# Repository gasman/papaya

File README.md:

# papAYa
an AY-3-8912 sound chip expansion board for the Raspberry Pi

## Why?
[I do ZX Spectrum chiptune performances](http://gasman.zxdemo.org/), but taking an entire ZX Spectrum setup to a venue is a faff, especially at gigs where the organisers are more used to people rocking up with a Gameboy, plugging in a jack and being ready to play. Some of the tracks I play require two sound chips, and taking two Spectrums would be even more of a faff.

Sure, you can emulate it, and honestly the AY is well-understood and deterministic enough that it would make no difference to the sound. But if you take that attitude, then what's the point of live music anyhow? I figure you don't need a 1980s-vintage Spectrum to be authentic, but you do at least need the actual sound chip.

Basically, I want to be as cool as the Gameboy folks. I want to get up on stage and make magic happen from a handheld device like I'm piloting a goddamn spaceship. And the best way to do that is to hook up an AY chip (or two) to a Raspberry Pi.

## What's here

* `papaya/` - KiCad files for the single-AY board
* `papaya2/` - KiCad files for the double-AY board
* `player/` - Command-line players for .psg files (as exported by [AY Emulator](https://bulba.untergrund.net/emulator_e.htm) and [Fuse](http://fuse-emulator.sourceforge.net/)). Requires [pigpio](http://abyz.me.uk/rpi/pigpio/) to build.
  * `player/psg` - plays a single-AY track in .psg format. Run with `sudo ./psg somefile.psg`
  * `player/psg2` - plays a dual-AY track exported as two .psg files. Run with `sudo ./psg2 somefile1.psg somefile2.psg`
* `server/` - Server software; see below
* `client/` - Client software to communicate with the papaya server
* `psgfiles/` - some example .psg files

## Bill of materials

For the single-AY board:
* Papaya v1 PCB
* P1 - 2x20 pin GPIO header https://www.adafruit.com/product/2222
* J1 - dual RCA connector [PJRAN2X1U01AUX](https://www.mouser.co.uk/ProductDetail/Switchcraft/PJRAN2X1U01AUX?qs=mcPJWgAPNre69iQqys4MXw%3D%3D)
* U1 - AY-3-8912 sound chip (_not_ AY-3-8912A - see below)
* R1, R2 - 10k resistor
* R3, R4 - 15k resistor

For the dual-AY board:

* Papaya 2 PCB
* P1 - 2x20 pin GPIO header https://www.adafruit.com/product/2222
* J1 - dual RCA connector [PJRAN2X1U01AUX](https://www.mouser.co.uk/ProductDetail/Switchcraft/PJRAN2X1U01AUX?qs=mcPJWgAPNre69iQqys4MXw%3D%3D)
* U1, U2 - AY-3-8912 sound chip (_not_ AY-3-8912A - see below)
* R1, R2, R5, R6 - 10k resistor
* R3, R4, R7, R8 - 15k resistor

## Design considerations
The AY data bus (pins DA0-DA7) is connected directly to GPIO pins: 17, 27, 22, 10, 9, 11, 5, 6. The AY chip is a 5V device while the Raspberry Pi runs on 3.3V, but since the data direction is write-only and the AY accepts anything over 2.5V as logic high, no level conversion is needed.

For the first AY chip, BC1 is on GPIO pin 13 and BDIR is on pin 19. On the dual AY board, the second chip's BC1 is on pin 20 and BDIR is on pin 21. The clock signal is provided by the Raspberry Pi's hardware clock on GPIO pin 4. GPIO pin 26 is connected to RESET on both chips (NOTE: this is not implemented on the PCB yet).

Audio output is in ACB stereo format: channel A (of both chips) is mixed to the left, channel B to the right and C in the centre.

Some or all AY-3-8912A chips have a quirk where the RESET line must be toggled low then high in order to activate the noise generator - it does not function immediately on power-on. This is implemented in the software, but the PCB has not yet been updated to support this (the RESET line is held high instead) and so will currently only work with AY-3-8912 (not 8912A) chips.

Technically this board doesn't qualify as a HAT, as it doesn't include the identifying EPROM.

## Mounting
With socketed chips, the Raspberry Pi and papAYa combo fits neatly into a [SmartiPi Touch 2 case](https://thepihut.com/products/smartipi-touch-2) with a [15mm back cover](https://thepihut.com/products/smartipi-touch-2-back-cover), provided you use [11mm spacers](https://thepihut.com/products/raspberry-pi-hat-mounting-kit) rather than the slightly-taller ones that come with the touchscreen.

## Server
Rather than having each client program do its own low-level GPIO access (which typically requires running as root), the AY can be made available over a network service, running on TCP port 8912. See server/protocol.txt for details of the protocol.

To build, run `make` from the `server` directory - this requires [pigpio](http://abyz.me.uk/rpi/pigpio/). Copy the resulting `server` executable to `/usr/local/sbin/papaya`, and run it under supervisor using a configuration file such as (in `/etc/supervisor/conf.d/papaya.conf`):

    [program:papaya]
    command=/usr/local/sbin/papaya
    autostart=true
    autorestart=true

`client/psg.py` is a client program for playing .psg files, written in Python - run with:

    ./psg.py somefile.psg

Or, for multiple chips:

    ./psg.py somefile1.psg somefile2.psg

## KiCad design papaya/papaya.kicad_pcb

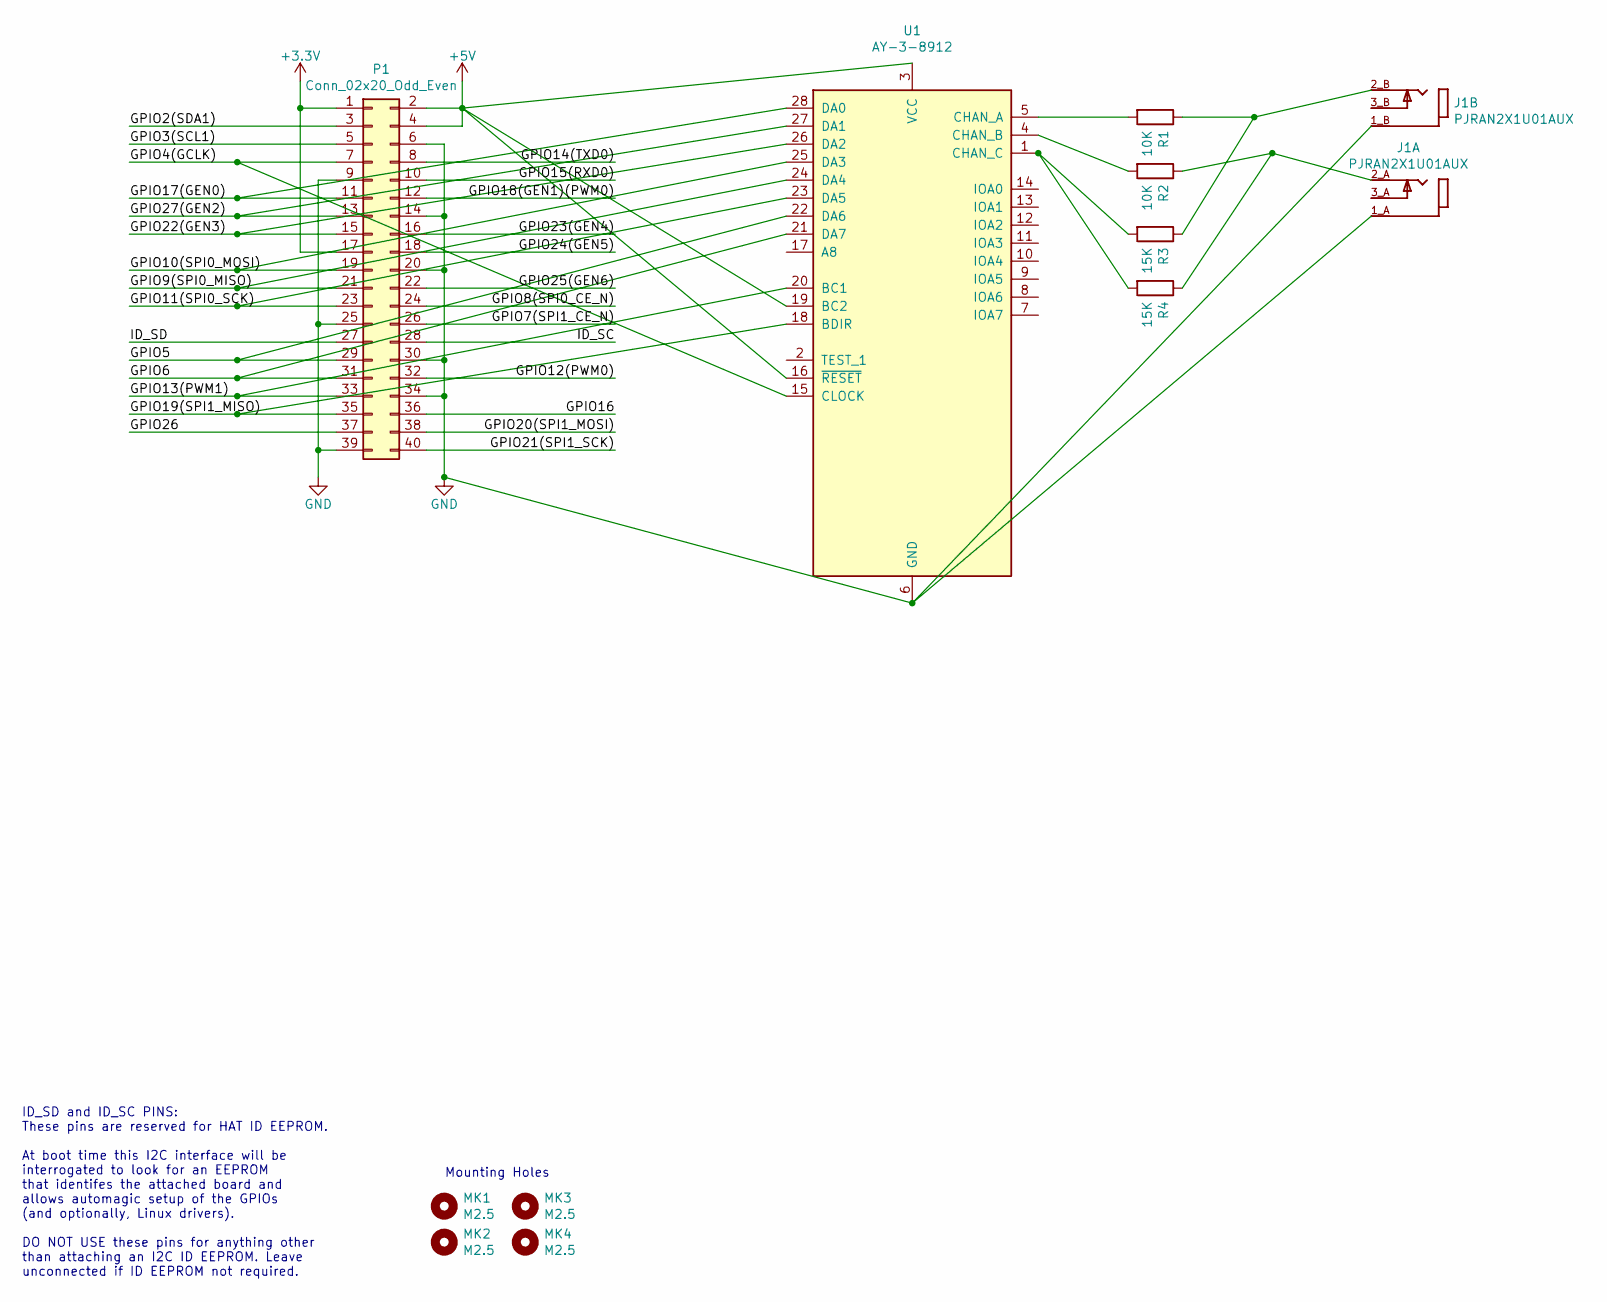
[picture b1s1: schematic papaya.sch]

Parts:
J1: PJRAN2X1U01AUX; SWITCHCRAFT_PJRAN2X1U01AUX
MK1, MK2, MK3, MK4: M2.5; MountingHole_2.7mm_M2.5
P1: Conn_02x20_Odd_Even; PinSocket_2x20_P2.54mm_Vertical
R1, R2: 10K; R_Axial_DIN0207_L6.3mm_D2.5mm_P10.16mm_Horizontal
R3, R4: 15K; R_Axial_DIN0207_L6.3mm_D2.5mm_P10.16mm_Horizontal
U1: AY-3-8912; DIP-28_W15.24mm_LongPads

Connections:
+3V3: P1.1, P1.17
+5V: P1.2, P1.4, U1.3 (VCC), U1.16 (~RESET~), U1.19 (BC2)
/GPIO2(SDA1): P1.3
/GPIO3(SCL1): P1.5
/GPIO5: P1.29, U1.22 (DA6)
/GPIO6: P1.31, U1.21 (DA7)
/GPIO8(SPI0_CE_N): P1.24
/GPIO9(SPI0_MISO): P1.21, U1.24 (DA4)
/GPIO10(SPI0_MOSI): P1.19, U1.25 (DA3)
/GPIO11(SPI0_SCK): P1.23, U1.23 (DA5)
/GPIO12(PWM0): P1.32
/GPIO13(PWM1): P1.33, U1.20 (BC1)
/GPIO14(TXD0): P1.8
/GPIO15(RXD0): P1.10
/GPIO16: P1.36
/GPIO17(GEN0): P1.11, U1.28 (DA0)
/GPIO18(GEN1)(PWM0): P1.12
/GPIO19(SPI1_MISO): P1.35, U1.18 (BDIR)
/GPIO20(SPI1_MOSI): P1.38
/GPIO21(SPI1_SCK): P1.40
/GPIO22(GEN3): P1.15, U1.26 (DA2)
/GPIO23(GEN4): P1.16
/GPIO24(GEN5): P1.18
/GPIO25(GEN6): P1.22
/GPIO26: P1.37
/GPIO27(GEN2): P1.13, U1.27 (DA1)
/ID_SC: P1.28
/ID_SD: P1.27
GND: J1.1_A (SLEEVE-A), J1.1_B (SLEEVE-B), P1.6, P1.9, P1.14, P1.20, P1.25, P1.30, P1.34, P1.39, U1.6 (GND)
unnamed: J1.2_A (TIP-A), R2.1, R4.1
unnamed: J1.2_B (TIP-B), R1.1, R3.1
unnamed: R1.2, U1.5 (CHAN_A)
unnamed: R2.2, U1.4 (CHAN_B)
unnamed: R3.2, R4.2, U1.1 (CHAN_C)

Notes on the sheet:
ID_SD and ID_SC PINS: These pins are reserved for HAT ID EEPROM. At boot time this I2C interface will be interrogated to look for an EEPROM that identifes the attached board and allows automagic setup of the GPIOs (and optionally, Linux drivers). DO NOT USE these pins for anything other than attach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
Mounting Holes

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
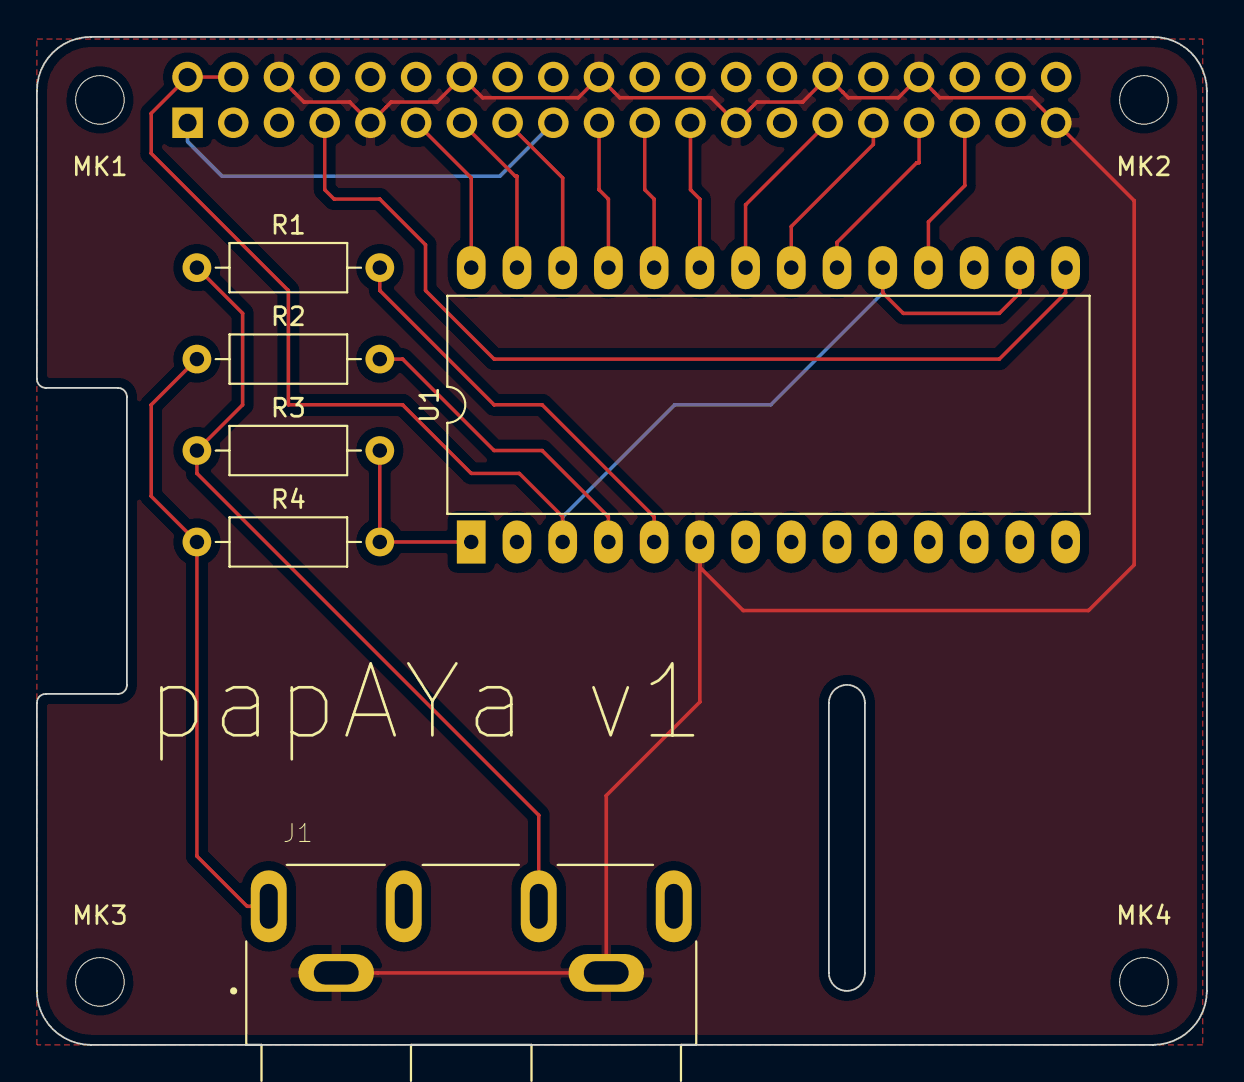
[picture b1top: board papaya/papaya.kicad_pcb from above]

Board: 2 copper layers, 65.0 x 56.0 mm, 11 parts (1 on the bottom side), 19 nets.

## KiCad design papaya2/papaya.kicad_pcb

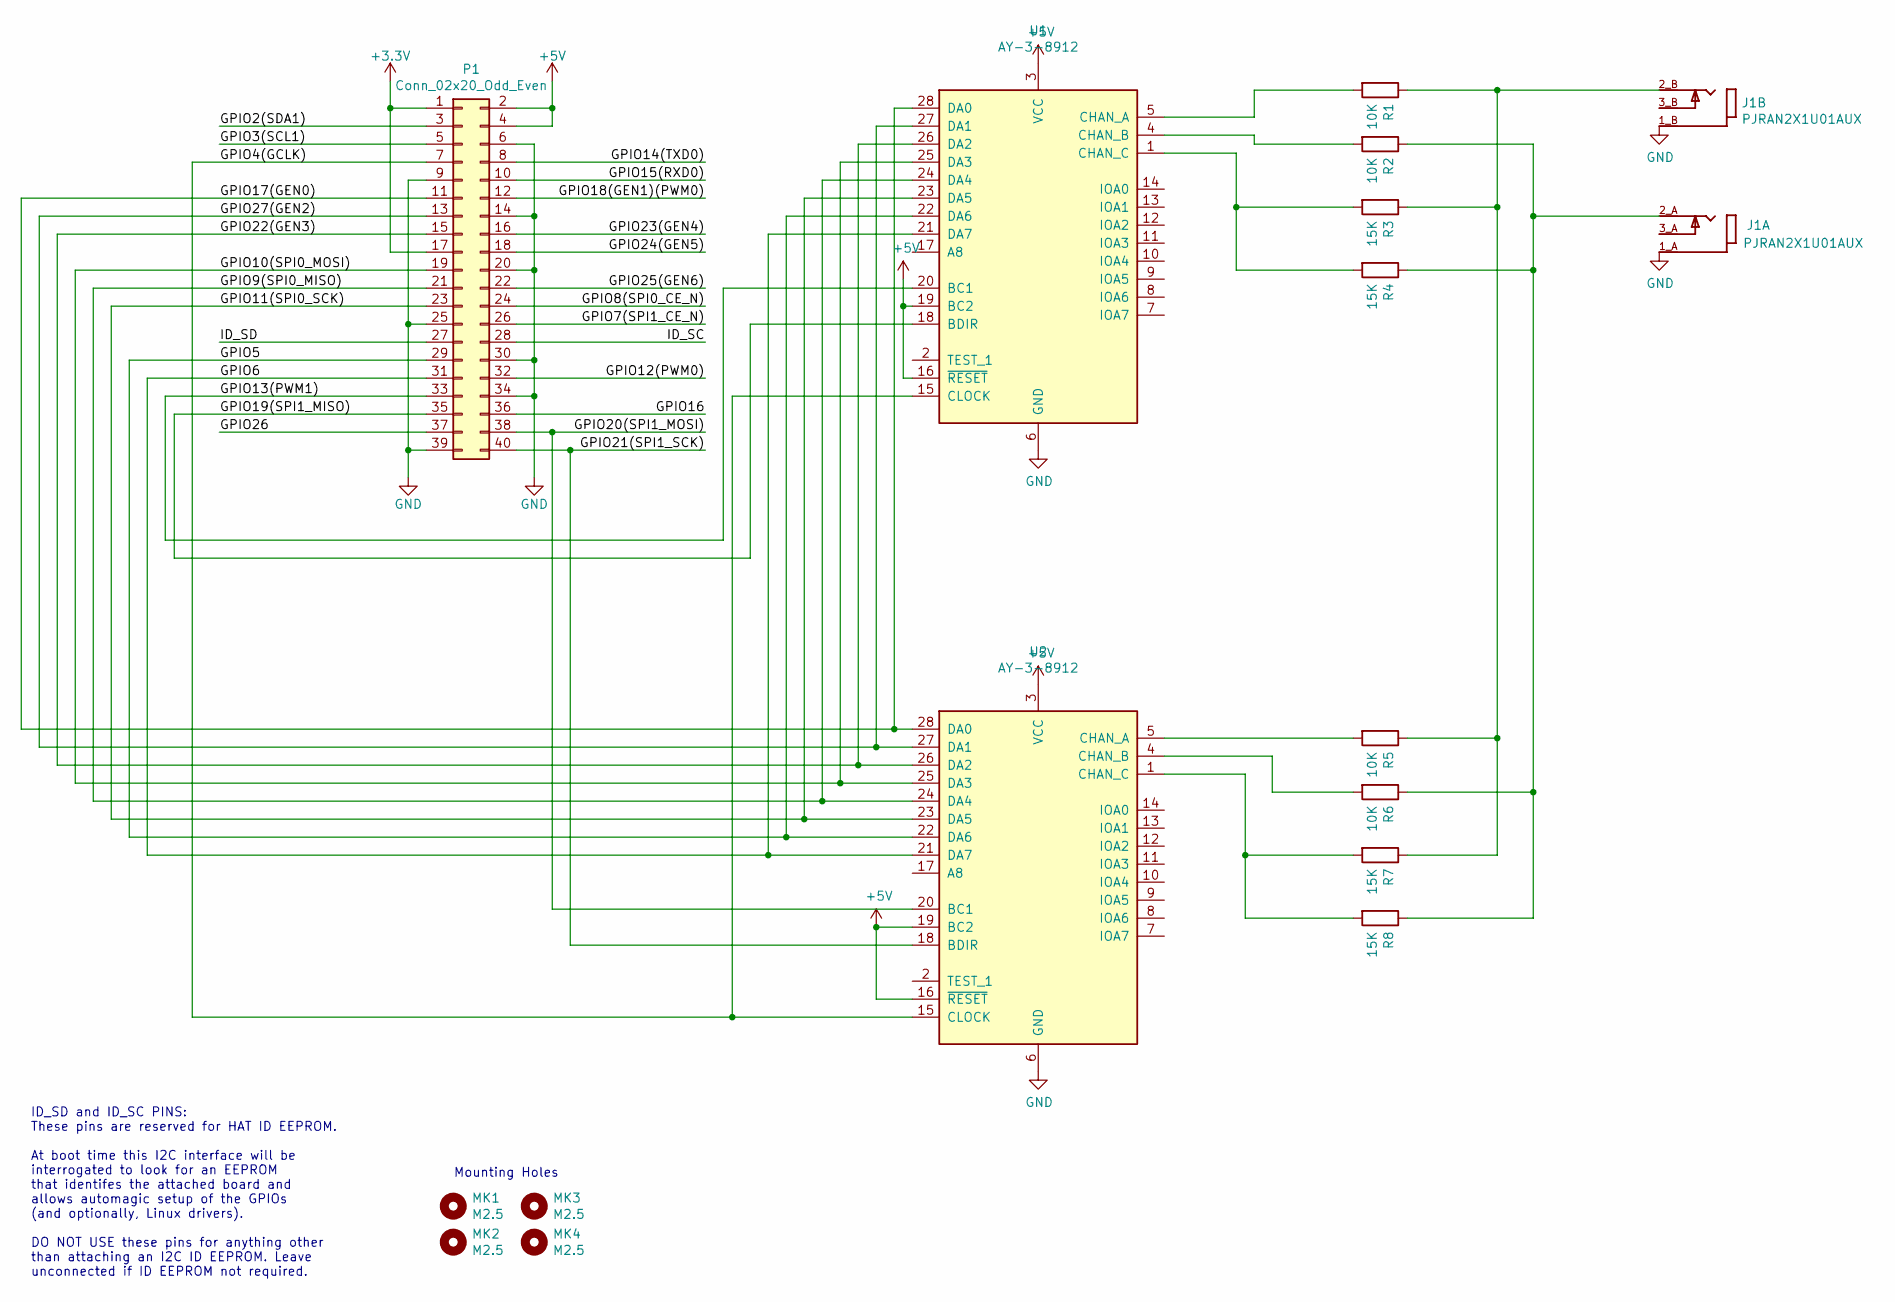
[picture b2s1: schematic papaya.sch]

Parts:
J1: PJRAN2X1U01AUX; SWITCHCRAFT_PJRAN2X1U01AUX
MK1, MK2, MK3, MK4: M2.5; MountingHole_2.7mm_M2.5
P1: Conn_02x20_Odd_Even; PinSocket_2x20_P2.54mm_Vertical
R1, R2, R5, R6: 10K; R_Axial_DIN0207_L6.3mm_D2.5mm_P10.16mm_Horizontal
R3, R4, R7, R8: 15K; R_Axial_DIN0207_L6.3mm_D2.5mm_P10.16mm_Horizontal
U1, U2: AY-3-8912; DIP-28_W15.24mm_LongPads

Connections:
+3V3: P1.1, P1.17
+5V: P1.2, P1.4, U1.3 (VCC), U1.16 (~RESET~), U1.19 (BC2), U2.3 (VCC), U2.16 (~RESET~), U2.19 (BC2)
/GPIO2(SDA1): P1.3
/GPIO3(SCL1): P1.5
/GPIO4(GCLK): P1.7, U1.15 (CLOCK), U2.15 (CLOCK)
/GPIO5: P1.29, U1.22 (DA6), U2.22 (DA6)
/GPIO6: P1.31, U1.21 (DA7), U2.21 (DA7)
/GPIO7(SPI1_CE_N): P1.26
/GPIO8(SPI0_CE_N): P1.24
/GPIO9(SPI0_MISO): P1.21, U1.24 (DA4), U2.24 (DA4)
/GPIO10(SPI0_MOSI): P1.19, U1.25 (DA3), U2.25 (DA3)
/GPIO11(SPI0_SCK): P1.23, U1.23 (DA5), U2.23 (DA5)
/GPIO12(PWM0): P1.32
/GPIO13(PWM1): P1.33, U1.20 (BC1)
/GPIO14(TXD0): P1.8
/GPIO15(RXD0): P1.10
/GPIO16: P1.36
/GPIO17(GEN0): P1.11, U1.28 (DA0), U2.28 (DA0)
/GPIO18(GEN1)(PWM0): P1.12
/GPIO19(SPI1_MISO): P1.35, U1.18 (BDIR)
/GPIO20(SPI1_MOSI): P1.38, U2.20 (BC1)
/GPIO21(SPI1_SCK): P1.40, U2.18 (BDIR)
/GPIO22(GEN3): P1.15, U1.26 (DA2), U2.26 (DA2)
/GPIO23(GEN4): P1.16
/GPIO24(GEN5): P1.18
/GPIO25(GEN6): P1.22
/GPIO26: P1.37
/GPIO27(GEN2): P1.13, U1.27 (DA1), U2.27 (DA1)
/ID_SC: P1.28
/ID_SD: P1.27
GND: J1.1_A (SLEEVE-A), J1.1_B (SLEEVE-B), P1.6, P1.9, P1.14, P1.20, P1.25, P1.30, P1.34, P1.39, U1.6 (GND), U2.6 (GND)
unnamed: J1.2_A (TIP-A), R2.1, R4.1, R6.1, R8.1
unnamed: J1.2_B (TIP-B), R1.1, R3.1, R5.1, R7.1
unnamed: R1.2, U1.5 (CHAN_A)
unnamed: R2.2, U1.4 (CHAN_B)
unnamed: R3.2, R4.2, U1.1 (CHAN_C)
unnamed: R5.2, U2.5 (CHAN_A)
unnamed: R6.2, U2.4 (CHAN_B)
unnamed: R7.2, R8.2, U2.1 (CHAN_C)

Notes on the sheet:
ID_SD and ID_SC PINS: These pins are reserved for HAT ID EEPROM. At boot time this I2C interface will be interrogated to look for an EEPROM that identifes the attached board and allows automagic setup of the GPIOs (and optionally, Linux drivers). DO NOT USE these pins for anything other than attach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
Mounting Holes

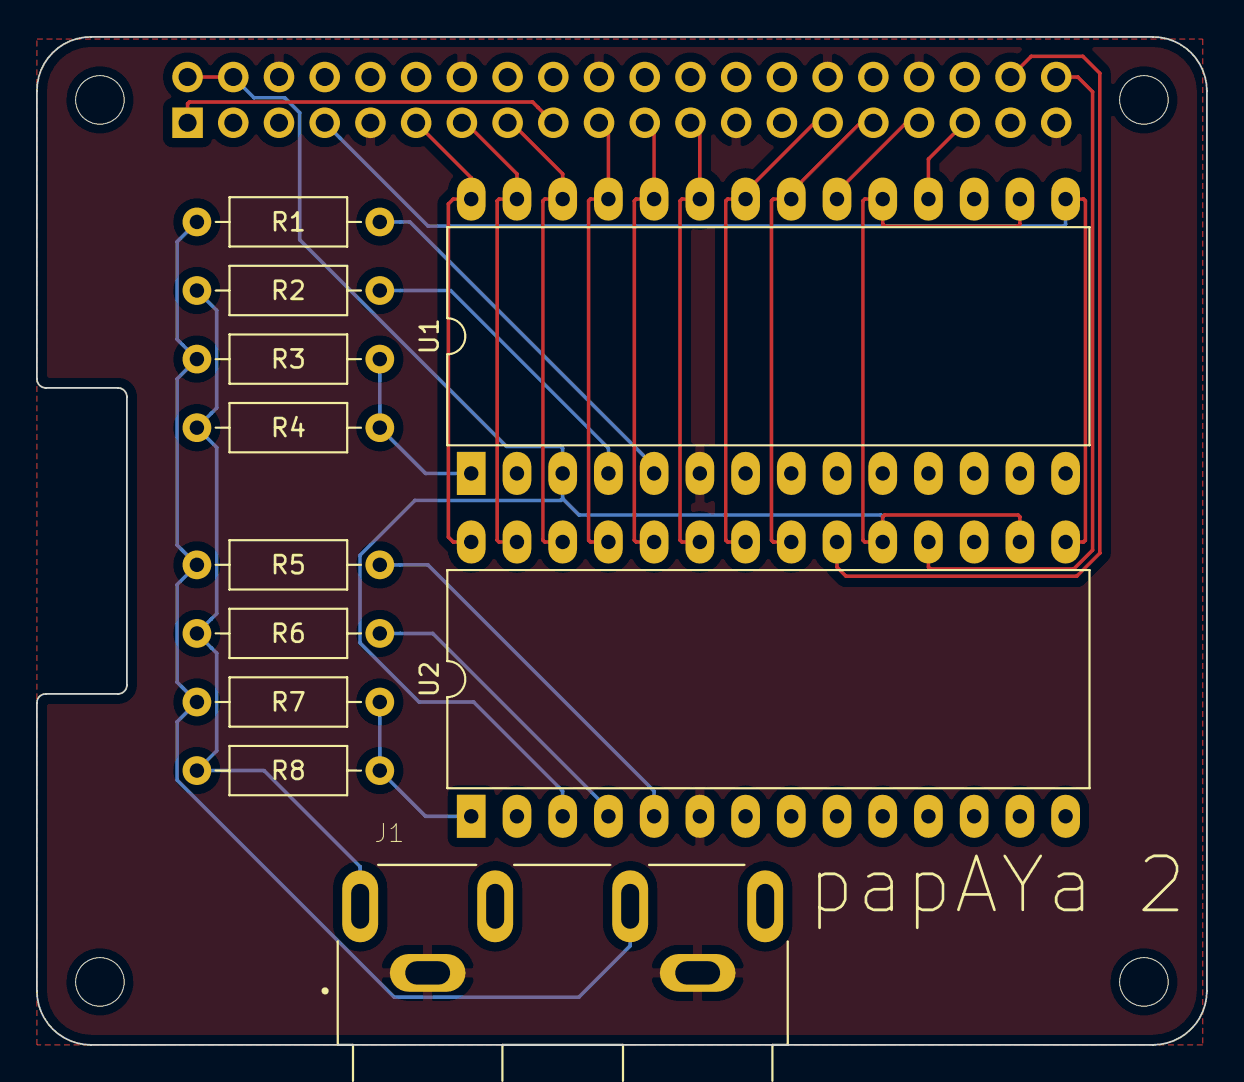
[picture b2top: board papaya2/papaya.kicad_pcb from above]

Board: 2 copper layers, 65.0 x 56.0 mm, 16 parts (1 on the bottom side), 24 nets.

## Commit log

2020-03-23 Add kicad files for papaya v1
2020-03-23 Add kicad files for papaya2
2020-03-23 Add readme + images
2020-03-23 Add player apps
2020-03-24 Add server implementation
2020-04-05 Add client program and example .psg files
2020-04-05 Refactor papaya communication into its own module
2020-04-05 Refactor PSG file handling into its own module
2020-04-05 extend PSG client to support multiple chips
2020-04-05 Accurate timing for PSG client
2020-04-05 multithread all the things
2020-04-05 First draft of the almighty Gasman concert control panel (also, variable framerate)
2020-11-27 Update ay.c to handle the reset line correctly
